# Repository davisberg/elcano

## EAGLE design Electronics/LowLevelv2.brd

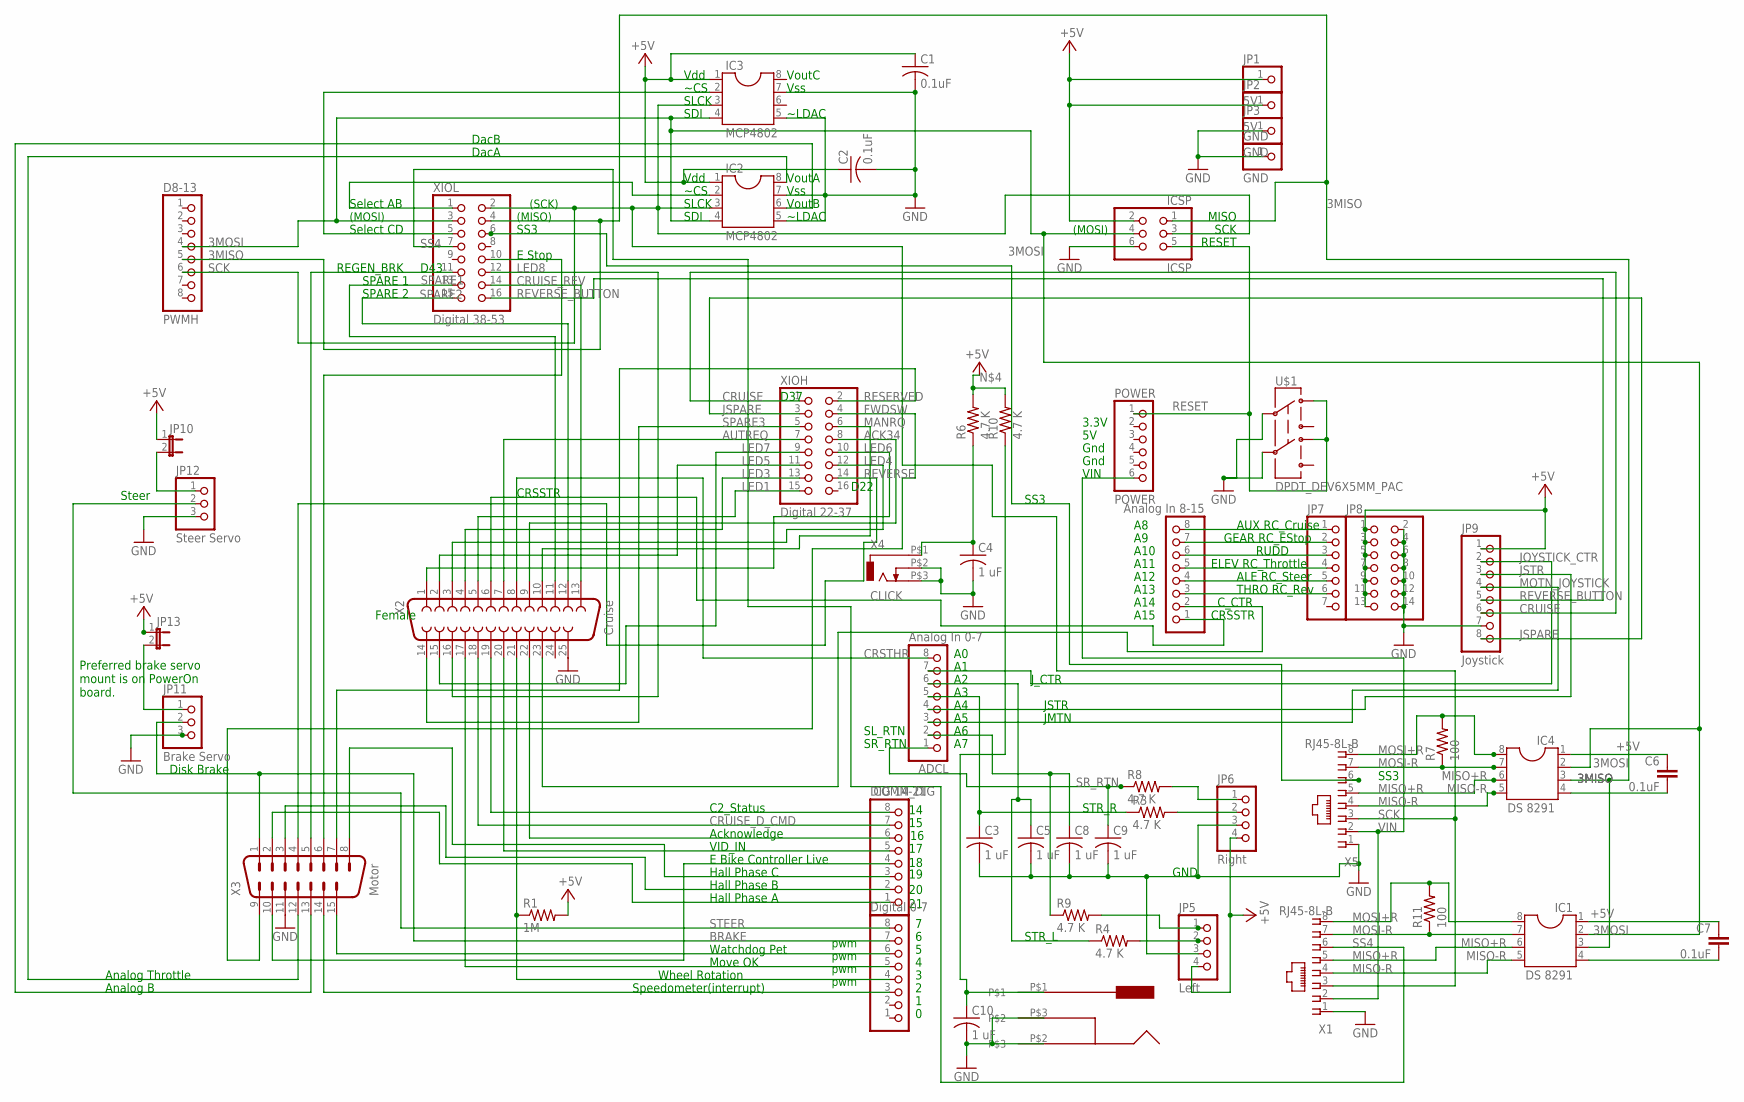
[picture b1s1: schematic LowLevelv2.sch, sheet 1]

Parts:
ADCH: Analog In 8-15; 1X08
ADCL: Analog In 0-7; 1X08
C1, C2: 0.1uF; C025-025X050
C3, C4, C5, C8, C9, C10: 1 uF; C025-030X050
C6, C7: 0.1uF; C2.5-2
COMM_DIG: DIG 14-21; 1X08
D8-13: PWMH; 1X08
GND: GND; 1X01
IC1, IC4: DS 8291; DIL08
IC2, IC3: MCP4802; DIL08
ICSP: ICSP; 2X03
JP1, JP2: 5V; 1X01
JP3: GND; 1X01
JP5: Left; 1X04/90
JP6: Right; 1X04/90
JP7: PINHD-1X7; 1X07
JP8: PINHD-2X7; 2X07
JP9: Joystick; 1X08/90
JP10, JP13: JP1E; JP1
JP11: Brake Servo; 1X03/90
JP12: Steer Servo; 1X03/90
POWER: POWER; 1X06
PWML: Digital 0-7; 1X08
R1: 1M; 0207/10
R3, R4, R6, R8, R9, R10: 4.7 K; 0207/10
R7, R11: 100; 0207/10
U$1: DPDT_DEV6X5MM_PAC; NEWSWITCH2_PAC
U$2: CUI_JACKTHROUGH_HOLE; CUIJACK
X1, X5: RJ45-8L-B; RJ45-NO-SHIELD
X2: Cruise; F25H
X3: Motor; 182-015-MALE
X4: CLICK; ODO_JACK
XIOH: Digital 22-37; 2X08
XIOL: Digital 38-53; 2X08

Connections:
1C: ADCH.6, JP7.3
3A: ADCH.3, JP7.6
3MISO: D8-13.5, IC1.3, IC4.3, ICSP.1, XIOL.4
3MOSI: D8-13.4, IC1.2, IC2.4, IC3.4, IC4.2, ICSP.4, XIOL.3
5V: JP10.2, JP12.1
5VOLT: JP11.1, JP13.2
+5V: C1.1, C2.1, C6.1, IC2.1, IC3.1, IC4.1, ICSP.2, JP1.1, JP2.1, JP5.4, JP6.4, JP8.1, JP8.3, JP8.5, JP8.7, JP8.9, JP8.11, JP8.13, JP9.1, JP10.1, JP13.1, R1.2, R6.2, R10.2
A14: ADCH.7, JP7.2
A15: ADCH.8, JP7.1
ACK34: X2.9, XIOH.8
ACKNOWLEDGE: COMM_DIG.6, X2.22
AUTREQ: X2.7, XIOH.7
BRAKE: JP11.2, PWML.7, X3.1
C2STATUS: COMM_DIG.8, X2.19
CRSSTR: ADCH.1, X2.6
CRSTHR: ADCL.8, X2.8
CRUISE: JP9.6, XIOH.1
CRUISE_D_CMD: COMM_DIG.7, X2.18
CRUISE_REV: X2.13, XIOL.14
C_CTR: ADCH.2, X2.23
DACA: IC2.8, X3.12
DACB: IC2.6, X3.13
EBIKECONTRL: COMM_DIG.4, X3.10
ESTOP: X3.6, XIOL.10
FWDSW: X3.9, XIOH.4
GND: C1.2, C2.2, C3.2, C4.2, C5.2, C8.2, C9.2, C10.2, GND.1, IC2.5, IC2.7, IC3.5, IC3.7, ICSP.6, JP3.1, JP5.3, JP6.3, JP8.2, JP8.4, JP8.6, JP8.8, JP8.10, JP8.12, JP8.14, JP9.7, JP11.3, JP12.3, U$1.PIN2 (2), U$1.PIN5 (5), U$2.P$2, U$2.P$3, X1.1, X2.25, X3.11, X4.P$2 (2), X4.P$3 (3), X5.1
HALLPHASEA: COMM_DIG.1, X3.2
HALLPHASEB: COMM_DIG.2, X3.3
HALLPHASEC: COMM_DIG.3, X3.8
JOYSTICK_CTR: ADCL.7, JP9.2
JSPARE: JP9.8, XIOH.3
JSTR: ADCL.4, JP9.3
LED1: X2.5, XIOH.15
LED3: X2.4, XIOH.13
LED4: X2.3, XIOH.12
LED5: X2.2, XIOH.11
LED6: X2.1, XIOH.10
LED7: X2.15, XIOH.9
LED8: X2.16, XIOL.12
L_STR: JP5.2, R4.2
MANRQ: X2.10, XIOH.6
MISO+R: IC1.6, IC4.6, X1.5, X5.5
MISO-R: IC1.5, IC4.5, X1.4, X5.4
MOSI+R: IC1.8, IC4.8, R7.2, R11.2, X1.8, X5.8
MOSI-R: IC1.7, IC4.7, R7.1, R11.1, X1.7, X5.7
MOTN_JOYSTICK: ADCL.3, JP9.4
MOVEOK: PWML.5, X2.17
unnamed: C10.1, R10.1, U$2.P$1
unnamed: C6.2, IC4.4
unnamed: C7.2, IC1.4
unnamed: C4.1, R6.1, X4.P$1 (1)
unnamed: C7.1, IC1.1
unnamed: ADCH.4, JP7.5
unnamed: ADCH.5, JP7.4
REGENBAKE: X3.5, XIOL.11
RESERVED: X3.7, XIOH.2
RESET: ICSP.5, POWER.1, U$1.PIN1 (1), U$1.PIN4 (4)
REVERSE: X3.4, XIOH.14
REVERSE_BUTTON: JP9.5, XIOL.16
R_STR: JP6.2, R3.2
SCK: D8-13.6, IC2.3, IC3.3, ICSP.3, X1.3, X5.3, XIOL.2
SELECTAB: IC2.2, XIOL.1
SELECTCD: IC3.2, XIOL.5
SL_RET: JP5.1, R9.2
SL_RTN: ADCL.2, C8.1, R9.1
SPARE1: X2.11, XIOL.13
SPARE2: X2.12, XIOL.15
SPARE3: X2.14, XIOH.5
SPEEDOMETER: PWML.3, X3.14
SR_RET: JP6.1, R8.2
SR_RTN: ADCL.1, C9.1, R8.1
SS3: X5.6, XIOL.6
SS4: X1.6, XIOL.7
STEER: JP12.2, PWML.8
STR_L: ADCL.6, C5.1, R4.1
STR_R: ADCL.5, C3.1, R3.1
VIDIN: COMM_DIG.5, X2.20
VIN: POWER.6, X1.2, X5.2
WATCHDOG: PWML.6, X3.15
WHEELROTATION: PWML.4, R1.1, X2.21

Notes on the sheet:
(MOSI)
pwm
(SCK)
(MISO)
Move OK
Disk Brake
Gnd
Steer
Acknowledge
VID_IN
C2_Status
REGEN_BRK
Female
Vdd
~CS
SLCK
VoutA
Vss
VoutB
~LDAC
VoutC
Select AB
Select CD
Watchdog Pet
Analog B
Analog Throttle
SDI
DacA
DacB
D43
3.3V
MISO
SCK
RESET
VIN
Wheel Rotation
Speedometer(interrupt)
AUX RC_Cruise
RUDD
ELEV RC_Throttle

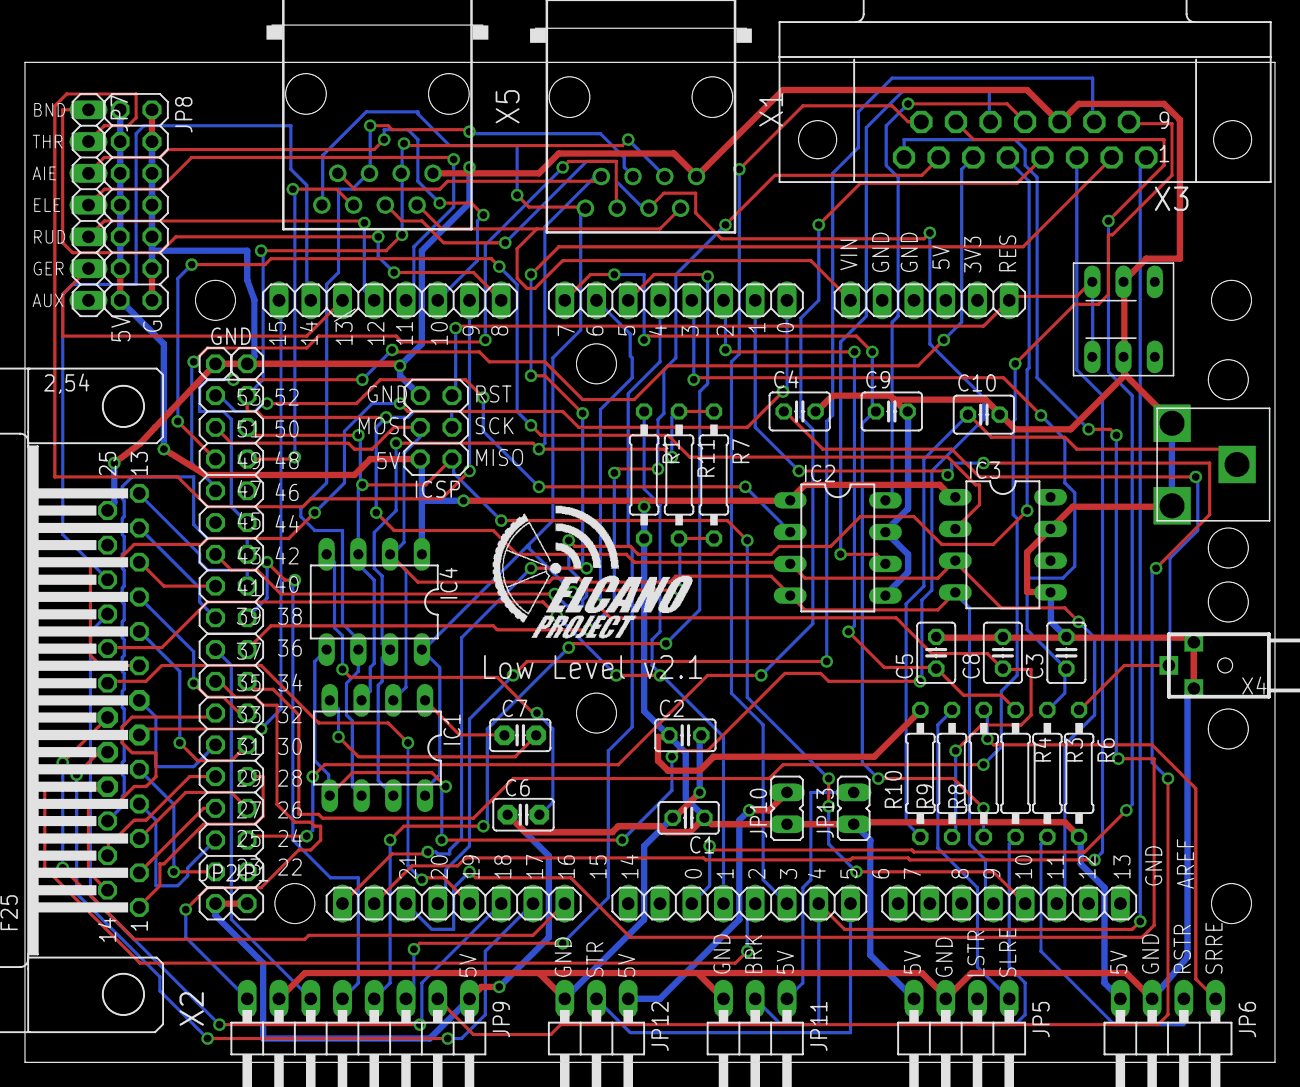
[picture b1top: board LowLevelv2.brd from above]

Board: 2 copper layers, 100.0 x 83.0 mm, 52 parts (0 on the bottom side), 80 nets.

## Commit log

2017-05-09 Add files via upload
    Added files for the LowLevel board.
